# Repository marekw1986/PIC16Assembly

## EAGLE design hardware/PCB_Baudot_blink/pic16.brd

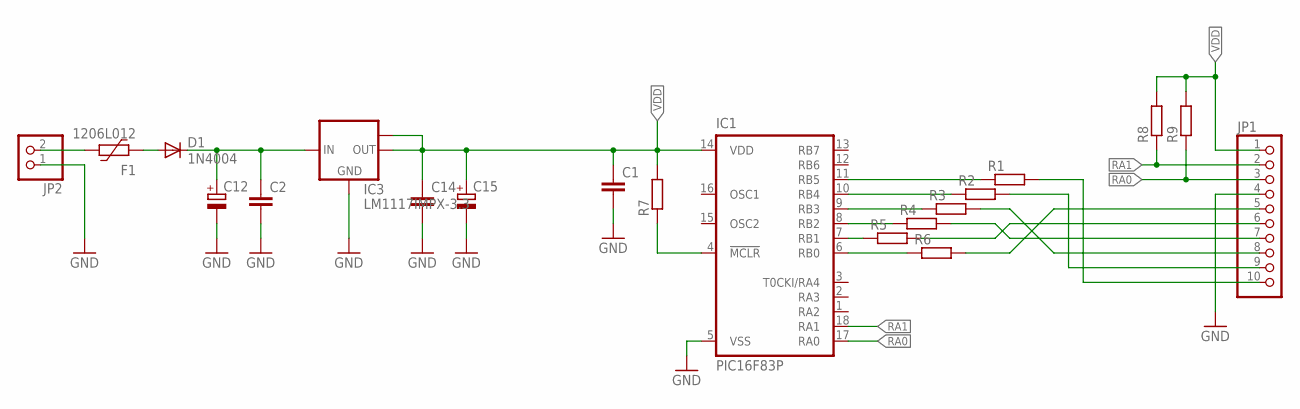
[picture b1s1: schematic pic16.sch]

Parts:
C1, C2, C14: C-EUC0603; C0603
C12, C15: CPOL-EUSMCB; SMC_B
D1: 1N4004; DO41-10
F1: 1206L012; 1206L
IC1: PIC16F83P; DIL18
IC3: LM1117IMPX-3.3; SOT223
JP1: PINHD-1X10; 1X10
JP2: PINHD-1X2; 1X02
R1, R2, R3, R4, R5, R6, R7: R-EU_R0603; R0603
R8, R9: R-EU_0204/5; 0204/5

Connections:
5V: C2.1, C12.+, D1.C, IC3.3 (IN)
GND: C1.2, C2.2, C12.-, C14.2, C15.-, IC1.5 (VSS), IC3.1 (GND), JP1.4, JP2.1
unnamed: JP1.8, R3.2
unnamed: JP1.7, R4.2
unnamed: JP1.6, R5.2
unnamed: JP1.5, R6.2
unnamed: JP1.9, R2.2
unnamed: JP1.10, R1.2
unnamed: IC1.11 (RB5), R1.1
unnamed: IC1.10 (RB4), R2.1
unnamed: IC1.9 (RB3), R3.1
unnamed: IC1.8 (RB2), R4.1
unnamed: IC1.7 (RB1), R5.1
unnamed: IC1.6 (RB0), R6.1
unnamed: IC1.4 (!MCLR), R7.1
unnamed: F1.1, JP2.2
unnamed: D1.A, F1.2
RA0: IC1.17 (RA0), JP1.3, R9.1
RA1: IC1.18 (RA1), JP1.2, R8.1
VDD: C1.1, C14.1, C15.+, IC1.14 (VDD), IC3.2 (OUT), IC3.TAB (OUT1), JP1.1, R7.2, R8.2, R9.2

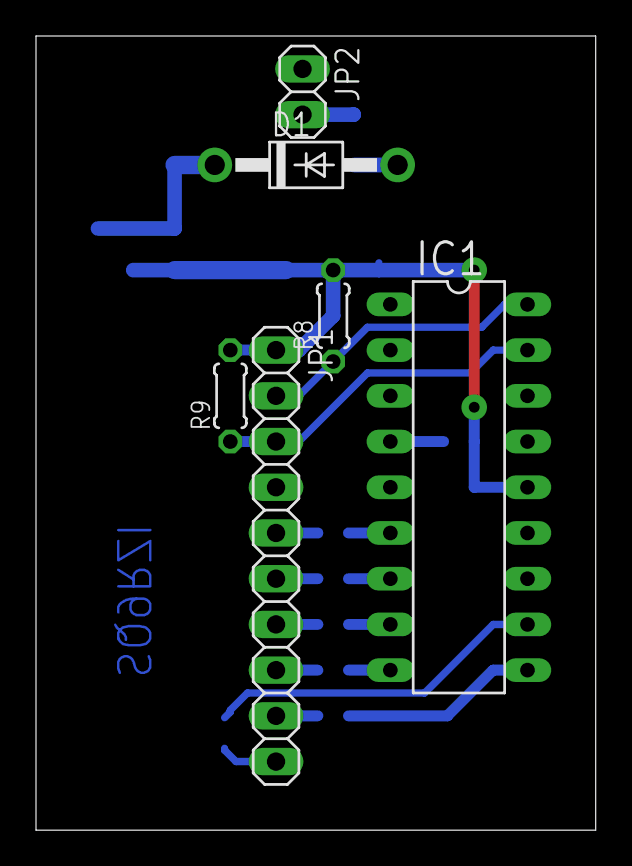
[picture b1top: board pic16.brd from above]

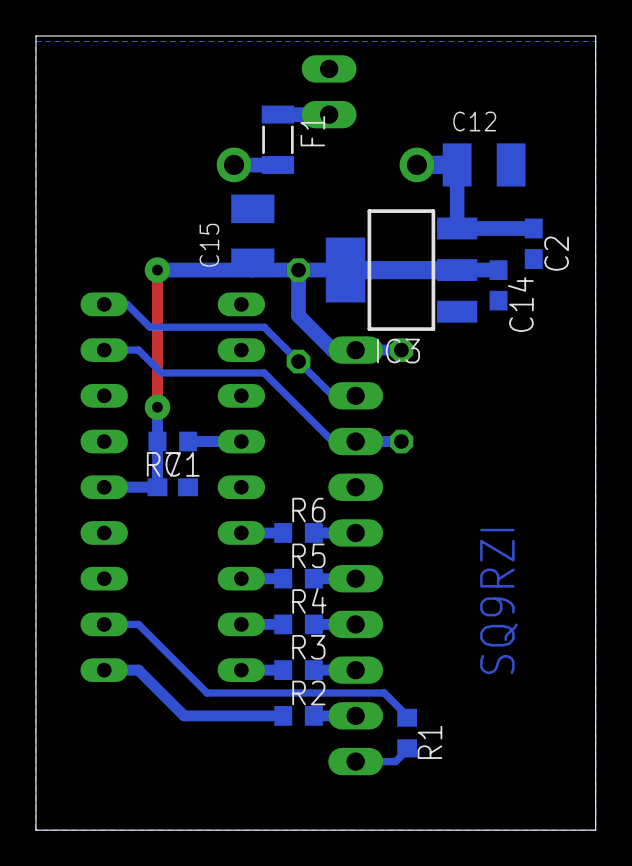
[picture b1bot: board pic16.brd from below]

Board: 2 copper layers, 31.1 x 44.1 mm, 20 parts (14 on the bottom side), 20 nets.

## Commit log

2024-07-28 Bug fixed
2024-07-28 NOPs removed
2024-07-28 Some bugs fixed
2024-07-29 Optimizations
2024-07-29 Python script generating text data
2024-07-29 Getting characters from table
2024-07-30 Reading text from table (work in progress)
2024-07-31 Problem with searchtable fixed
2024-07-31 Minor issues fixed
2024-07-31 Script update to generate baudot encoded hex values
2024-07-31 PCB added
2024-08-02 Timer resetted after input change
2024-08-05 Oscillator problem fixed
2024-08-05 LVP disabled
